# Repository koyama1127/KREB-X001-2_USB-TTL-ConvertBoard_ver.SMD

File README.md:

# KREB-X001-2_USB-TTL-ConvertBoard_ver.SMD
 KREB-X001のSMD部品バージョン  
 チップ部品を1608で統一  
 USBコネクタをType-Cに変更  
 各種機能及びピンアサインはKREB-X001と同一

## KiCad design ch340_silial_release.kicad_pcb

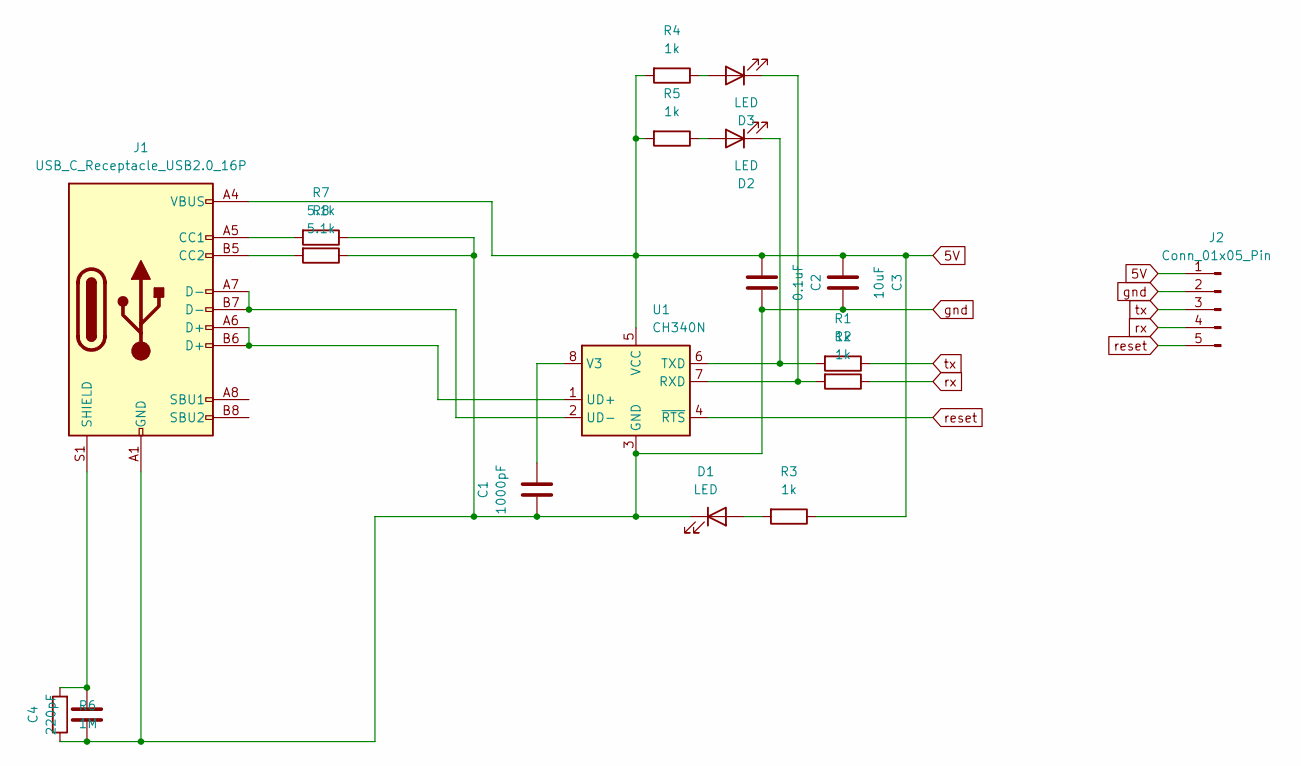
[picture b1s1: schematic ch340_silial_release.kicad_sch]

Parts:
C1: 1000pF; C_0603_1608Metric_Pad1.08x0.95mm_HandSolder
C2: 0.1uF; C_0603_1608Metric_Pad1.08x0.95mm_HandSolder
C3: 10uF; C_0603_1608Metric_Pad1.08x0.95mm_HandSolder
C4: 220pF; C_0805_2012Metric
D1, D2, D3: LED; LED_0603_1608Metric_Pad1.05x0.95mm_HandSolder
J1: USB_C_Receptacle_USB2.0_16P; USB_C_Receptacle_Palconn_UTC16-G
J2: Conn_01x05_Pin; PinHeader_1x05_P2.54mm_Vertical
R1, R2, R3, R4, R5: 1k; R_0805_2012Metric
R6: 1M; R_0805_2012Metric
R7, R8: 5.1k; R_0805_2012Metric
U1: CH340N; SOP-8_3.9x4.9mm_P1.27mm

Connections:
5V: C2.2, C3.2, J1.A4 (VBUS), J1.A9 (VBUS), J1.B4 (VBUS), J1.B9 (VBUS), J2.1, R3.1, R4.2, R5.2, U1.5 (VCC)
unnamed: D1.2 (A), R3.2
unnamed: D2.2 (A), R5.1
unnamed: D2.1 (K), R1.2, U1.6 (TXD)
unnamed: D3.2 (A), R4.1
unnamed: D3.1 (K), R2.2, U1.7 (RXD)
unnamed: J1.A5 (CC1), R7.2
unnamed: J1.B5 (CC2), R8.2
unnamed: C4.1, J1.S1 (SHIELD), R6.2
unnamed: J1.A6 (D+), J1.B6 (D+), U1.1 (UD+)
unnamed: J1.A7 (D-), J1.B7 (D-), U1.2 (UD-)
unnamed: C1.1, U1.8 (V3)
gnd: C1.2, C2.1, C3.1, C4.2, D1.1 (K), J1.A1 (GND), J1.A12 (GND), J1.B1 (GND), J1.B12 (GND), J2.2, R6.1, R7.1, R8.1, U1.3 (GND)
reset: J2.5, U1.4 (~RTS)
rx: J2.4, R2.1
tx: J2.3, R1.1

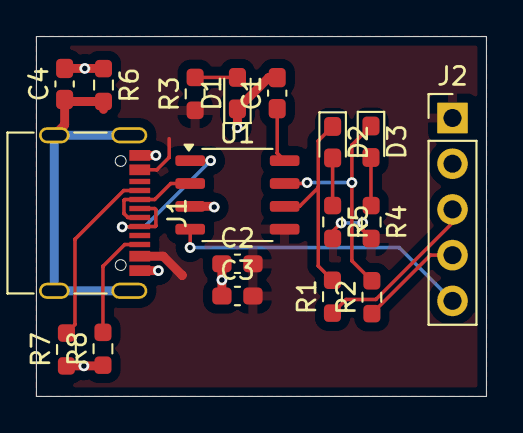
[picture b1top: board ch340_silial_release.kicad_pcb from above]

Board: 2 copper layers, 25.0 x 20.0 mm, 18 parts (0 on the bottom side), 16 nets.

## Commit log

2025-02-14 試作ver0.1
